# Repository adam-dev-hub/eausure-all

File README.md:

<div align="center">

<br/>

</div>

# EauSûre
Écosystème IoT de surveillance intelligente de la qualité de l'eau s'articule autour de trois composantes principales : une bouée connectée flottante chargée de la collecte des données, une passerelle LoRa développée en interne (DIY) assurant la transmission des mesures, ainsi qu'un environnement logiciel hétérogène regroupant des interfaces utilisateur, des API et une plateforme cloud pour le traitement, le stockage et la visualisation des données.

L'organisation regroupe les différents sous-systèmes de la solution :
- firmware embarqué du nœud de mesure et de la passerelle ;
- APIs fragmentées par responsabilité métier ;
- application mobile terrain ;
- interface web d'administration ;
- conception électronique, mécanique et modélisation système ;
- documentation technique et rapport d'ingénierie.

## Portée

EauSûre est conçu comme une plateforme complète, allant du matériel embarqué jusqu'aux interfaces de supervision.

- **Nœud de mesure** : acquisition des paramètres de qualité de l'eau, détection d'événements et communication LoRa sécurisée ;
- **Passerelle IoT** : jonction entre le terrain, le cloud, MQTT et les applications clientes ;
- **Backend fragmenté** : authentification, profil, administration, télémétrie et orchestration matérielle ;
- **Applications clientes** : usage mobile sur le terrain et supervision administrateur sur le web ;
- **Conception système** : SysML, PCB, modélisation 3D et documentation de projet.

## Dépôts principaux

- `EauSure_Firmware` : firmware du nœud de mesure et de la passerelle ;
- `EauSure_User_MobileApp` : application mobile terrain ;
- `EauSure_Admin_Dashboard_Website` : portail web d'administration ;
- `EauSure_Hardware_API` : orchestration matérielle et télémétrie ;
- `EauSure_Admin_API` : administration, pré-enregistrement et releases firmware ;
- `EauSure_Auth_API` : authentification et identité ;
- `EauSure_Profile_API` : profil utilisateur ;
- `EauSure_PCB` : conception électronique ;
- `EauSure_3D` : conception mécanique.

## Rapport

- PDF du rapport d'ingénierie : [Consulter le rapport EauSûre](https://1drv.ms/b/c/14e06c77a7dac468/IQCNwBGUbkDMTaTTdn0Hem94AVIdE5QvMWrk3accX1DUpic?e=Vb73pf)

## Architecture

- **Terrain** : nœud de mesure + passerelle ;
- **Communication** : LoRa, BLE, Wi-Fi, MQTT, HTTPS ;
- **Cloud** : APIs spécialisées, base de données, stockage firmware ;
- **Clients** : application mobile et portail web administrateur.      

## Stack

- ESP32 / FreeRTOS
- LoRa / BLE / Wi-Fi / MQTT
- Node.js / Express / TypeScript
- Next.js / React Native / Expo
- MongoDB
- KiCad / Fusion 360 / SysML / PlantUML

## Finalité

L'objectif d'EauSûre est de proposer une chaîne cohérente de surveillance de la qualité de l'eau, couvrant :
- la mesure embarquée ;
- la communication sécurisée ;
- la supervision en temps réel ;
- la maintenance et les mises à jour distantes ;
- la traçabilité technique de bout en bout.

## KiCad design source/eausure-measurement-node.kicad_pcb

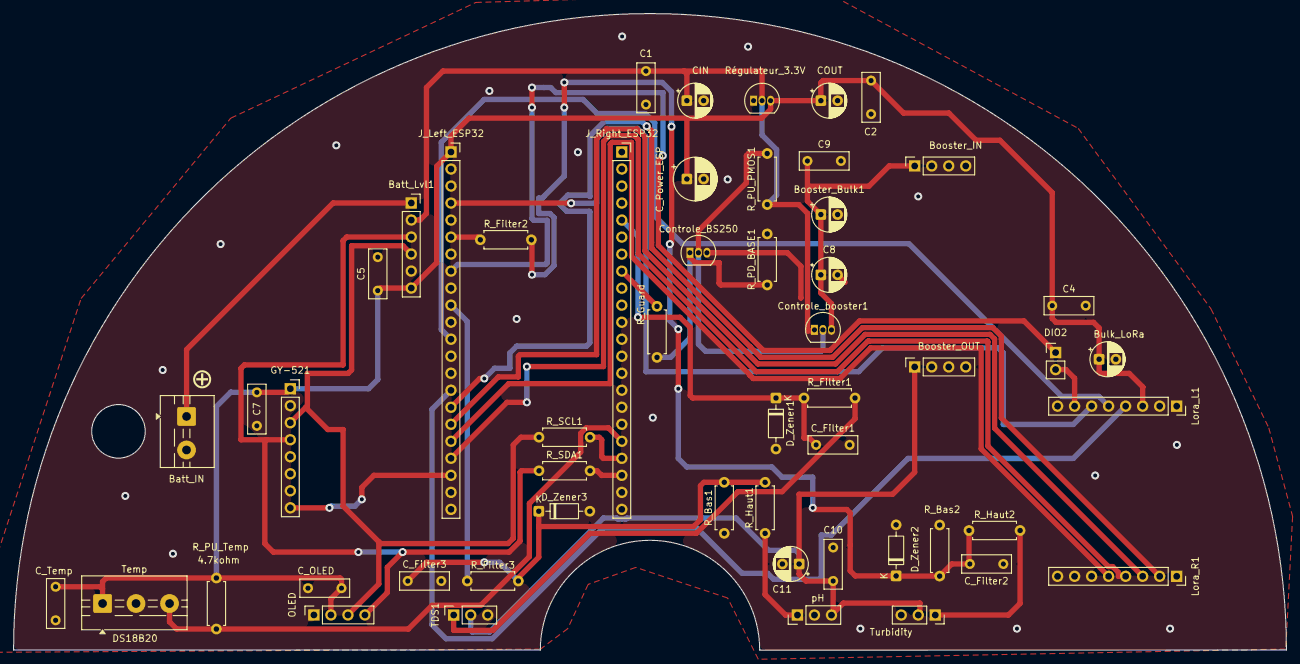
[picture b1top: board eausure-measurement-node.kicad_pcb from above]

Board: 2 copper layers, 190.0 x 95.0 mm, 53 parts (0 on the bottom side), 32 nets.

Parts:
Batt_IN: 2xS14500; TerminalBlock_MaiXu_MX126-5.0-02P_1x02_P5.00mm
Batt_Lvl1: INA219; PinSocket_1x06_P2.54mm_Vertical
Booster_Bulk1: 220uF; CP_Radial_D5.0mm_P2.50mm
Booster_IN: IN; PinSocket_1x04_P2.54mm_Vertical
Booster_OUT: OUT; PinSocket_1x04_P2.54mm_Vertical
Bulk_LoRa: 100uF; CP_Radial_D5.0mm_P2.50mm
C1, C2, C4, C5, C7, C9, C10: 100nF; C_Rect_L7.2mm_W2.5mm_P5.00mm
C8, C11: 10uF; CP_Radial_D5.0mm_P2.50mm
CIN: 10uF; CP_Radial_D5.0mm_P2.50mm
COUT: 10uF; CP_Radial_D5.0mm_P2.50mm
C_Filter1, C_Filter2, C_Filter3: 100nF; C_Rect_L7.2mm_W2.5mm_P5.00mm
C_OLED: 100nF; C_Rect_L7.2mm_W2.5mm_P5.00mm
C_Power_ESP: 470uF; CP_Radial_D6.3mm_P2.50mm
C_Temp: 100nF; C_Rect_L7.2mm_W2.5mm_P5.00mm
Controle_BS250: BC547; TO-92_Inline
Controle_booster1: BS250; TO-92_Inline
DIO2: A/D DIO2; PinHeader_1x02_P2.54mm_Vertical
D_Zener1, D_Zener2, D_Zener3: ESD_Safe; D_DO-35_SOD27_P7.62mm_Horizontal
GY-521: MPU6050; PinSocket_1x08_P2.54mm_Vertical
J_Left_ESP32: 22_PIN; PinSocket_1x22_P2.54mm_Vertical
J_Right_ESP32: 22_PIN; PinSocket_1x22_P2.54mm_Vertical
Lora_L1: 8_PIN; PinSocket_1x08_P2.54mm_Vertical
Lora_R1: 8_PIN; PinSocket_1x08_P2.54mm_Vertical
OLED: SSD1306; PinSocket_1x04_P2.54mm_Vertical
R_Bas1, R_Bas2: 10Kohm; R_Axial_DIN0207_L6.3mm_D2.5mm_P7.62mm_Horizontal
R_Filter1, R_Filter2, R_Filter3: 4.7Kohm; R_Axial_DIN0207_L6.3mm_D2.5mm_P7.62mm_Horizontal
R_Guard: 1Kohm; R_Axial_DIN0207_L6.3mm_D2.5mm_P7.62mm_Horizontal
R_Haut1, R_Haut2: 15Kohm; R_Axial_DIN0207_L6.3mm_D2.5mm_P7.62mm_Horizontal
R_PD_BASE1: 100Kohm; R_Axial_DIN0207_L6.3mm_D2.5mm_P7.62mm_Horizontal
R_PU_PMOS1: 100kohm; R_Axial_DIN0207_L6.3mm_D2.5mm_P7.62mm_Horizontal
R_PU_Temp: 4.7kohm; R_Axial_DIN0207_L6.3mm_D2.5mm_P7.62mm_Horizontal
R_SCL1: 47ohm; R_Axial_DIN0207_L6.3mm_D2.5mm_P7.62mm_Horizontal
R_SDA1: 47ohm; R_Axial_DIN0207_L6.3mm_D2.5mm_P7.62mm_Horizontal
Régulateur_3.3V: MCP1700; TO-92_Inline
TDS1: SEN0244; PinSocket_1x03_P2.54mm_Vertical
Temp: DS18B20; TerminalBlock_MaiXu_MX126-5.0-03P_1x03_P5.00mm
Turbidity: SEN0189; PinSocket_1x03_P2.54mm_Vertical
pH: E201; PinHeader_1x03_P2.54mm_Vertical

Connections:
unnamed: Batt_IN.1, Batt_Lvl1.1 (VIN+)
unnamed: Batt_IN.2, Batt_Lvl1.5 (GND), Booster_Bulk1.2, Booster_IN.4 (VIN-), Booster_OUT.4 (VOUT-), Bulk_LoRa.2, C1.2, C2.2, C4.2, C5.2, C7.1, C8.2, C9.2, C10.1, C11.2, CIN.2, COUT.2, C_Filter1.2, C_Filter2.2, C_Filter3.2, C_OLED.2, C_Power_ESP.2, C_Temp.1, Controle_BS250.3 (E), D_Zener1.2 (A), D_Zener2.2 (A), D_Zener3.2 (A), GY-521.2 (GND), J_Left_ESP32.22 (GND), J_Right_ESP32.1 (GND1), J_Right_ESP32.21 (GND2), J_Right_ESP32.22 (GND3), Lora_L1.1 (GND1), Lora_L1.2 (GND2), Lora_R1.1 (GND1), Lora_R1.8 (GND2), OLED.1 (GND), R_Bas1.1, R_Bas2.1, R_PD_BASE1.2, Régulateur_3.3V.1 (GND), TDS1.3 (-), Temp.2 (GND), Turbidity.3 (-), pH.2 (-)
unnamed: Batt_Lvl1.4 (SCL), GY-521.3 (SCL), OLED.3 (SCL), R_SCL1.1
unnamed: Batt_Lvl1.3 (SDA), GY-521.4 (SDA), OLED.4 (SDA), R_SDA1.1
unnamed: Batt_Lvl1.6 (VCC), Bulk_LoRa.1, C2.1, C4.1, C5.1, C7.2, COUT.1, C_OLED.1, C_Power_ESP.1, C_Temp.2, GY-521.1 (VCC), J_Left_ESP32.1 (3V_1), Lora_L1.3 (3V3), OLED.2 (VCC), R_PU_Temp.2, Régulateur_3.3V.3 (VO), Temp.1 (3V3)
unnamed: Batt_Lvl1.2 (VIN-), C1.1, CIN.1, Controle_booster1.1 (S), R_PU_PMOS1.1, Régulateur_3.3V.2 (VI)
unnamed: Booster_Bulk1.1, Booster_IN.1 (VIN+), C8.1, C9.1, Controle_booster1.3 (D)
unnamed: Booster_OUT.1 (VOUT+), C10.2, C11.1, TDS1.2 (+), Turbidity.2 (+), pH.3 (+)
unnamed: Controle_BS250.1 (B), R_Guard.2, R_PD_BASE1.1
unnamed: Controle_BS250.2 (C), Controle_booster1.2 (G), R_PU_PMOS1.2
unnamed: C_Filter1.1, D_Zener1.1 (K), J_Right_ESP32.5 (2), R_Filter1.1
unnamed: C_Filter2.1, D_Zener2.1 (K), R_Bas2.2, R_Filter2.2, R_Haut2.1
unnamed: C_Filter3.1, D_Zener3.1 (K), R_Bas1.2, R_Filter3.2, R_Haut1.2
unnamed: GY-521.8 (INT), J_Left_ESP32.20 (14)
unnamed: J_Left_ESP32.12 (8), Lora_L1.5 (DIO0)
unnamed: J_Left_ESP32.15 (9), Lora_L1.4 (RST)
unnamed: J_Left_ESP32.16 (10), Lora_R1.2 (NSS)
unnamed: J_Left_ESP32.17 (11), Lora_R1.3 (MOSI)
unnamed: J_Left_ESP32.18 (12), Lora_R1.5 (SCK)
unnamed: J_Left_ESP32.19 (13), Lora_R1.4 (MISO)
unnamed: DIO2.1, J_Left_ESP32.8 (15)
unnamed: J_Left_ESP32.10 (17), R_Filter3.1
unnamed: J_Left_ESP32.6, R_Filter2.1
unnamed: J_Right_ESP32.20 (19), R_SDA1.2
unnamed: J_Right_ESP32.19 (20), R_SCL1.2
unnamed: J_Right_ESP32.18 (21), R_PU_Temp.1, Temp.3 (DQ)
unnamed: J_Right_ESP32.8 (40), R_Guard.1
unnamed: DIO2.2, Lora_L1.7 (DIO2)
unnamed: J_Left_ESP32.4, Lora_L1.6 (DIO1)
unnamed: R_Filter1.2, TDS1.1 (AOUT)
unnamed: R_Haut2.2, Turbidity.1 (AOUT)
unnamed: R_Haut1.1, pH.1 (AOUT)

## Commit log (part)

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2026-05-18 Update README and implement firmware upload endpoint with file handling
2026-05-18 Refactor firmware release serialization and improve catalog endpoint response
2026-05-18 Fix catalog endpoint to handle default channel value correctly
2026-05-19 Add firmware inspection and preparation endpoints with version extraction
2026-05-21 Refactor code structure for improved readability and maintainability
2026-05-21 Update README to enhance visual presentation and formatting
2026-05-21 Update README to improve logo presentation and formatting
2026-05-21 Enhancing README.md with API documentation
2026-05-21 Refactor README.md layout for improved logo presentation and styling
2026-05-22 feat: add UserAvatar and WaterWaveBg components; enhance AuthContext with logging and token masking; implement MqttContext for MQTT communication; improve ProfileContext with caching and logging; upd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
2026-05-22 Code cleaning and reorganization the project structure, including renaming assets and updating components.
2026-05-30 eausure svg fix
